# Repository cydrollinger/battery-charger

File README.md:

<a href="https://elec-real.com/case-studies/battery-charger/"></img></a>

>Electronic Realization L.L.C.								   
>Design: Battery charger 4 Li cells		   
>Engineer: Cy Drollinger								   
>Date: 5/18												           
>Email: cy@elec-real.com	
>Website: https://elec-real.com							   
>Address: 2023 Stadium Dr Suite 2B #210 Bozeman, MT 59715				   
>Phone: 406-539-8117	

**NOTE:**
 This design has been tested and functions as specified. The design is provided gratis, so, please 
 think critically while utilizing and or redesigning. Open electronic circuitry can be dangerous due 
 to easily shorting circuits which can generate immediate and intense heat resulting in fire. Conversation is
 welcome to improve this design and repository, but, be advised ER is a professional design house and
 monetary compensation is required for additional work toward this design enabling your success.			   

**PURPOSE:**
This is a hardware design that is capable of charging 4 Li ion cells. The design employs four different circuits
and charge currents: 100mA, 200mA, 400mA, and 800mA. The design files were created with Eagle Cadsoft v7.7 as a 
two layer board. Free Eagle version would be capable of viewing, and editing these files for redesign. 

>**File Arcitecture with a terse description**

* FOLDERS:
	* docs		: datasheets charging IC and battery holder
	* hardware	: eagle cadsoft(v7.7) hardware design files 	
		* eagleup		: 3D files 
		* library		: eagle part files 
		* manufacturing	: files required to produce the design
			* bom	: files created to order the parts
					* batteryCharger.txt	: 
					* batteryv1.1.csv	: digikey order
					* hundredUnits.txt	
			* gerber	: files generated to manufacture the board
			* <a href="https://oshpark.com/shared_projects/4os8OxLZ"></img></a>
	* readme.md	: this file

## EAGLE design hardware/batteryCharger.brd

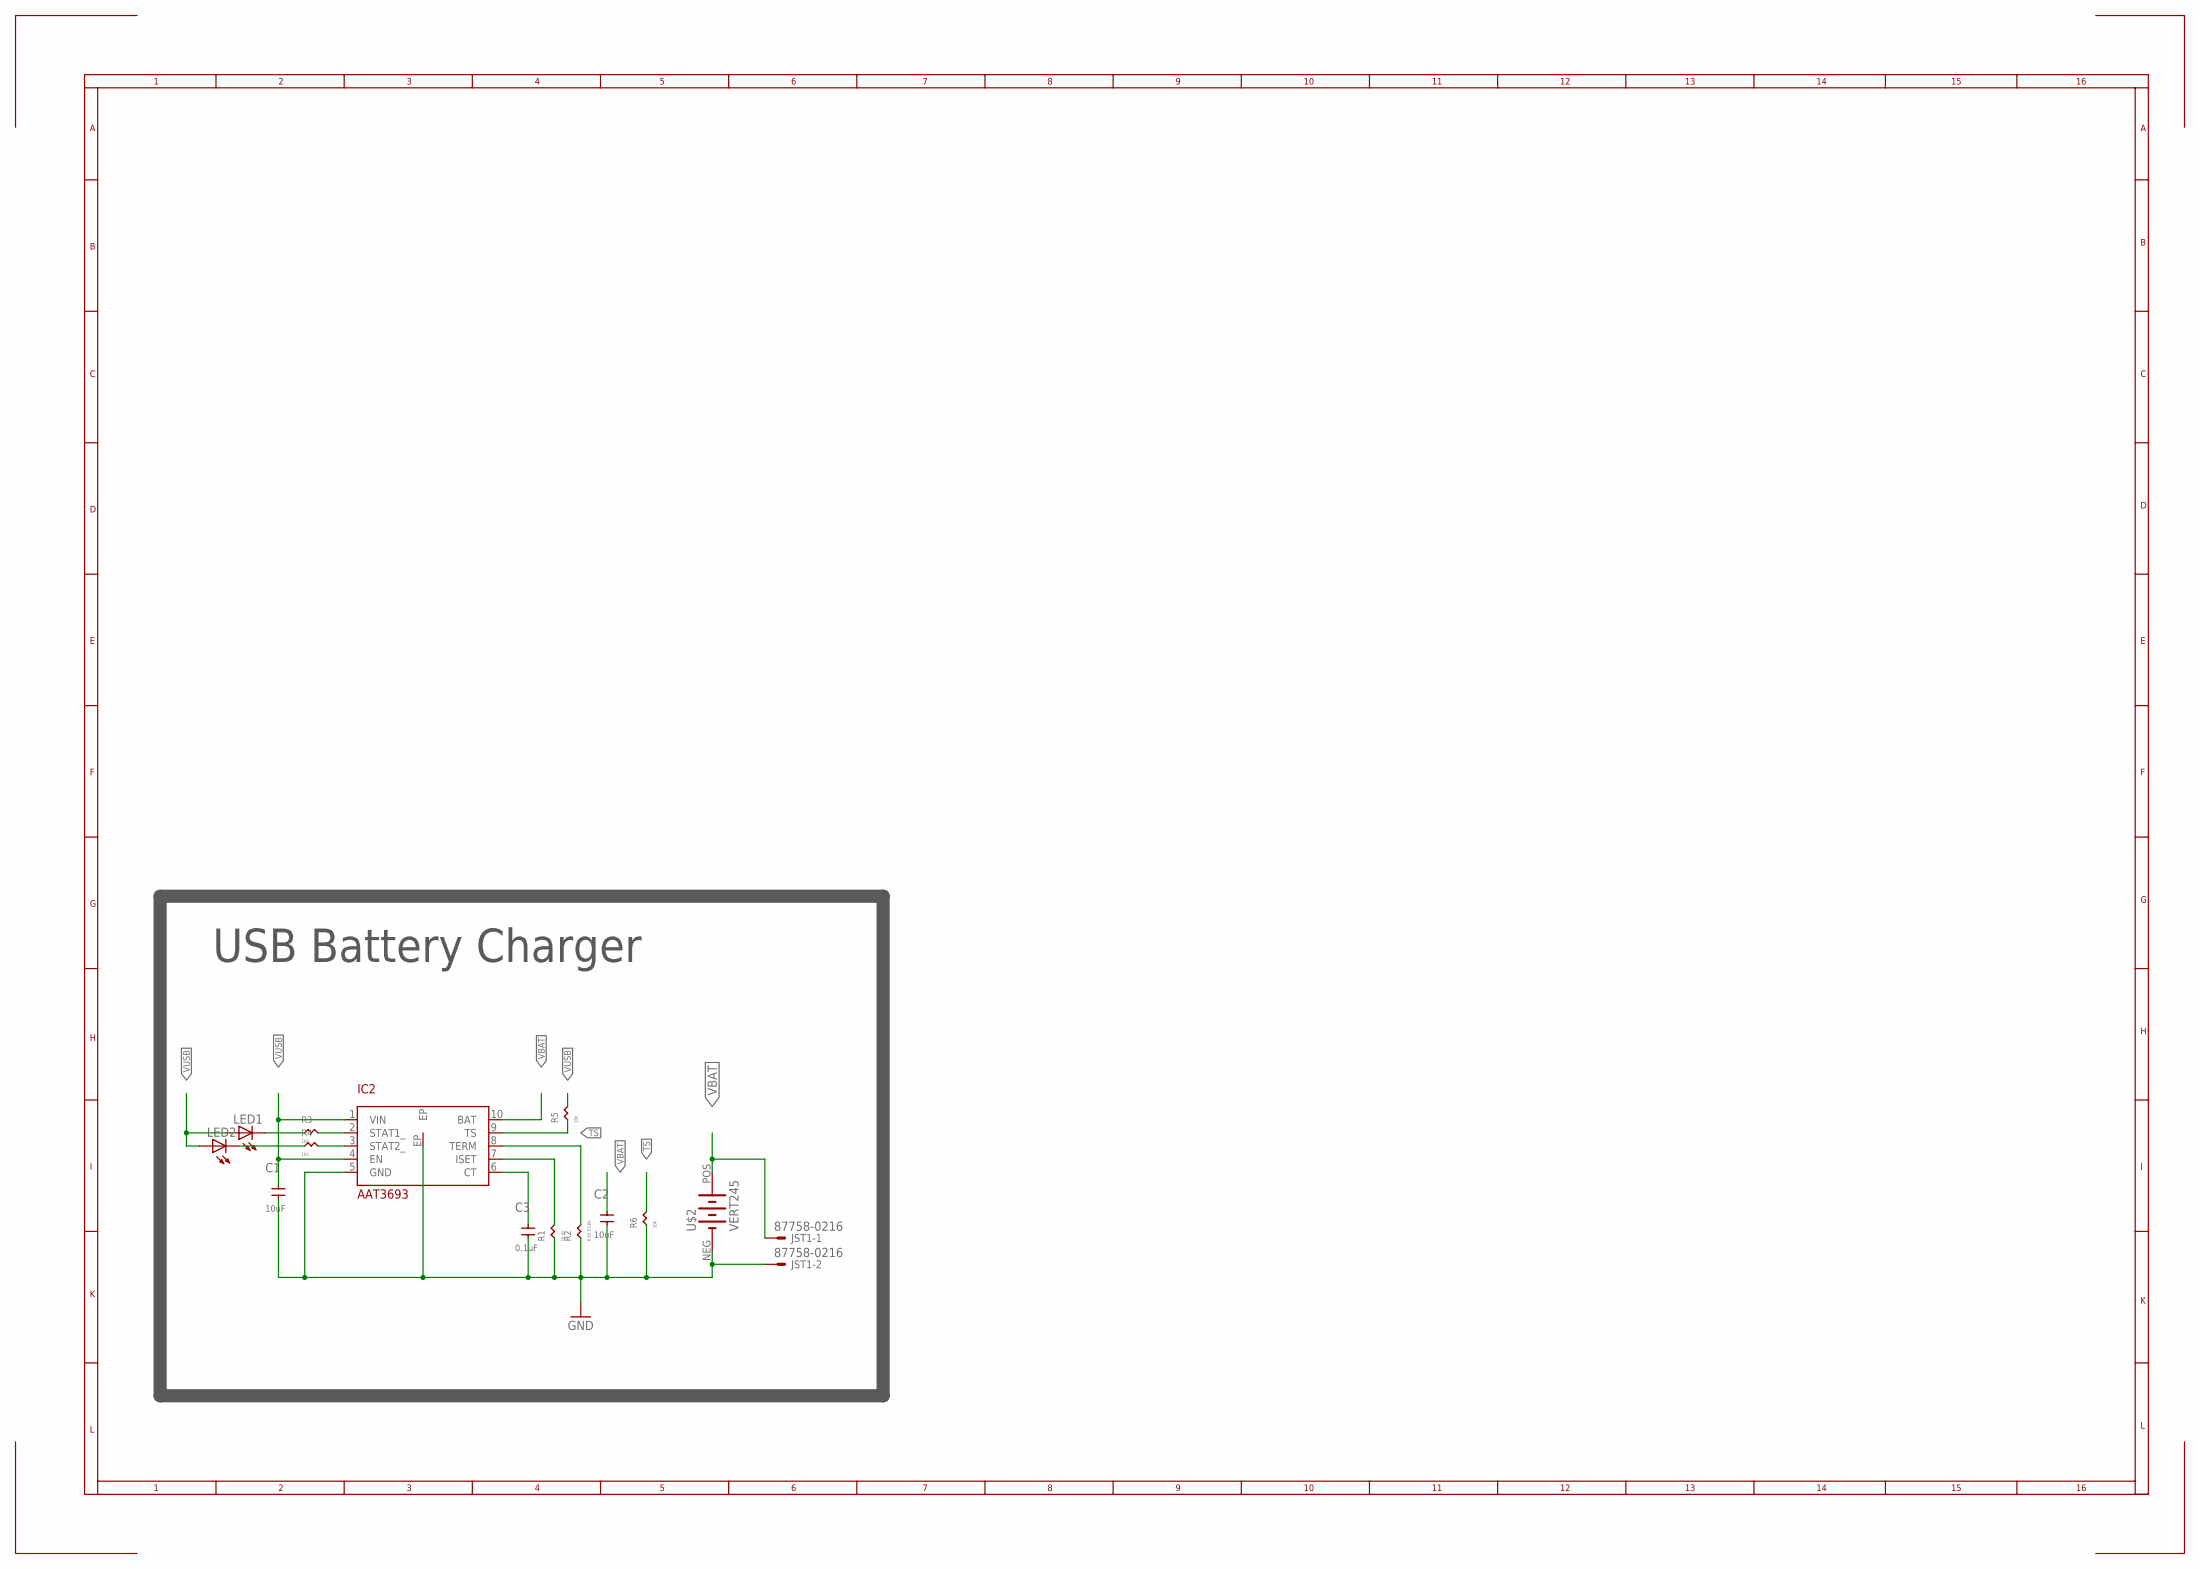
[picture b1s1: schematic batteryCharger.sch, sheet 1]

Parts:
C1, C2: 10uF; C0805
C3: 0.1uF; C0402
IC2: AAT3693
JST1: 87758-0216
LED1, LED2: LEDCHIP-LED0603; CHIP-LED0603
R1: 16.5k; R0402
R2: 6.65-53.6k; R0402
R3, R4: 1k5; R0402
R5, R6: 10k; R0402
U$2: VERT245

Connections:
GND: C1.1, C2.1, C3.1, IC2.5 (GND), IC2.EP, JST1.2, R1.1, R2.1, R6.1, U$2.NEG (-); also elsewhere on the board
unnamed: C3.2, IC2.6 (CT)
unnamed: IC2.7 (ISET), R1.2
unnamed: IC2.8 (TERM), R2.2
unnamed: IC2.3 (STAT2_), R4.2
unnamed: IC2.2 (STAT1_), R3.2
unnamed: LED1.C, R3.1
unnamed: LED2.C, R4.1
TS: IC2.9 (TS), R5.1, R6.2
VBAT: C2.2, IC2.10 (BAT), JST1.1, U$2.POS (+)
VUSB: C1.2, IC2.1 (VIN), IC2.4 (EN), LED1.A, LED2.A, R5.2; also elsewhere on the board

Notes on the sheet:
USB Battery Charger

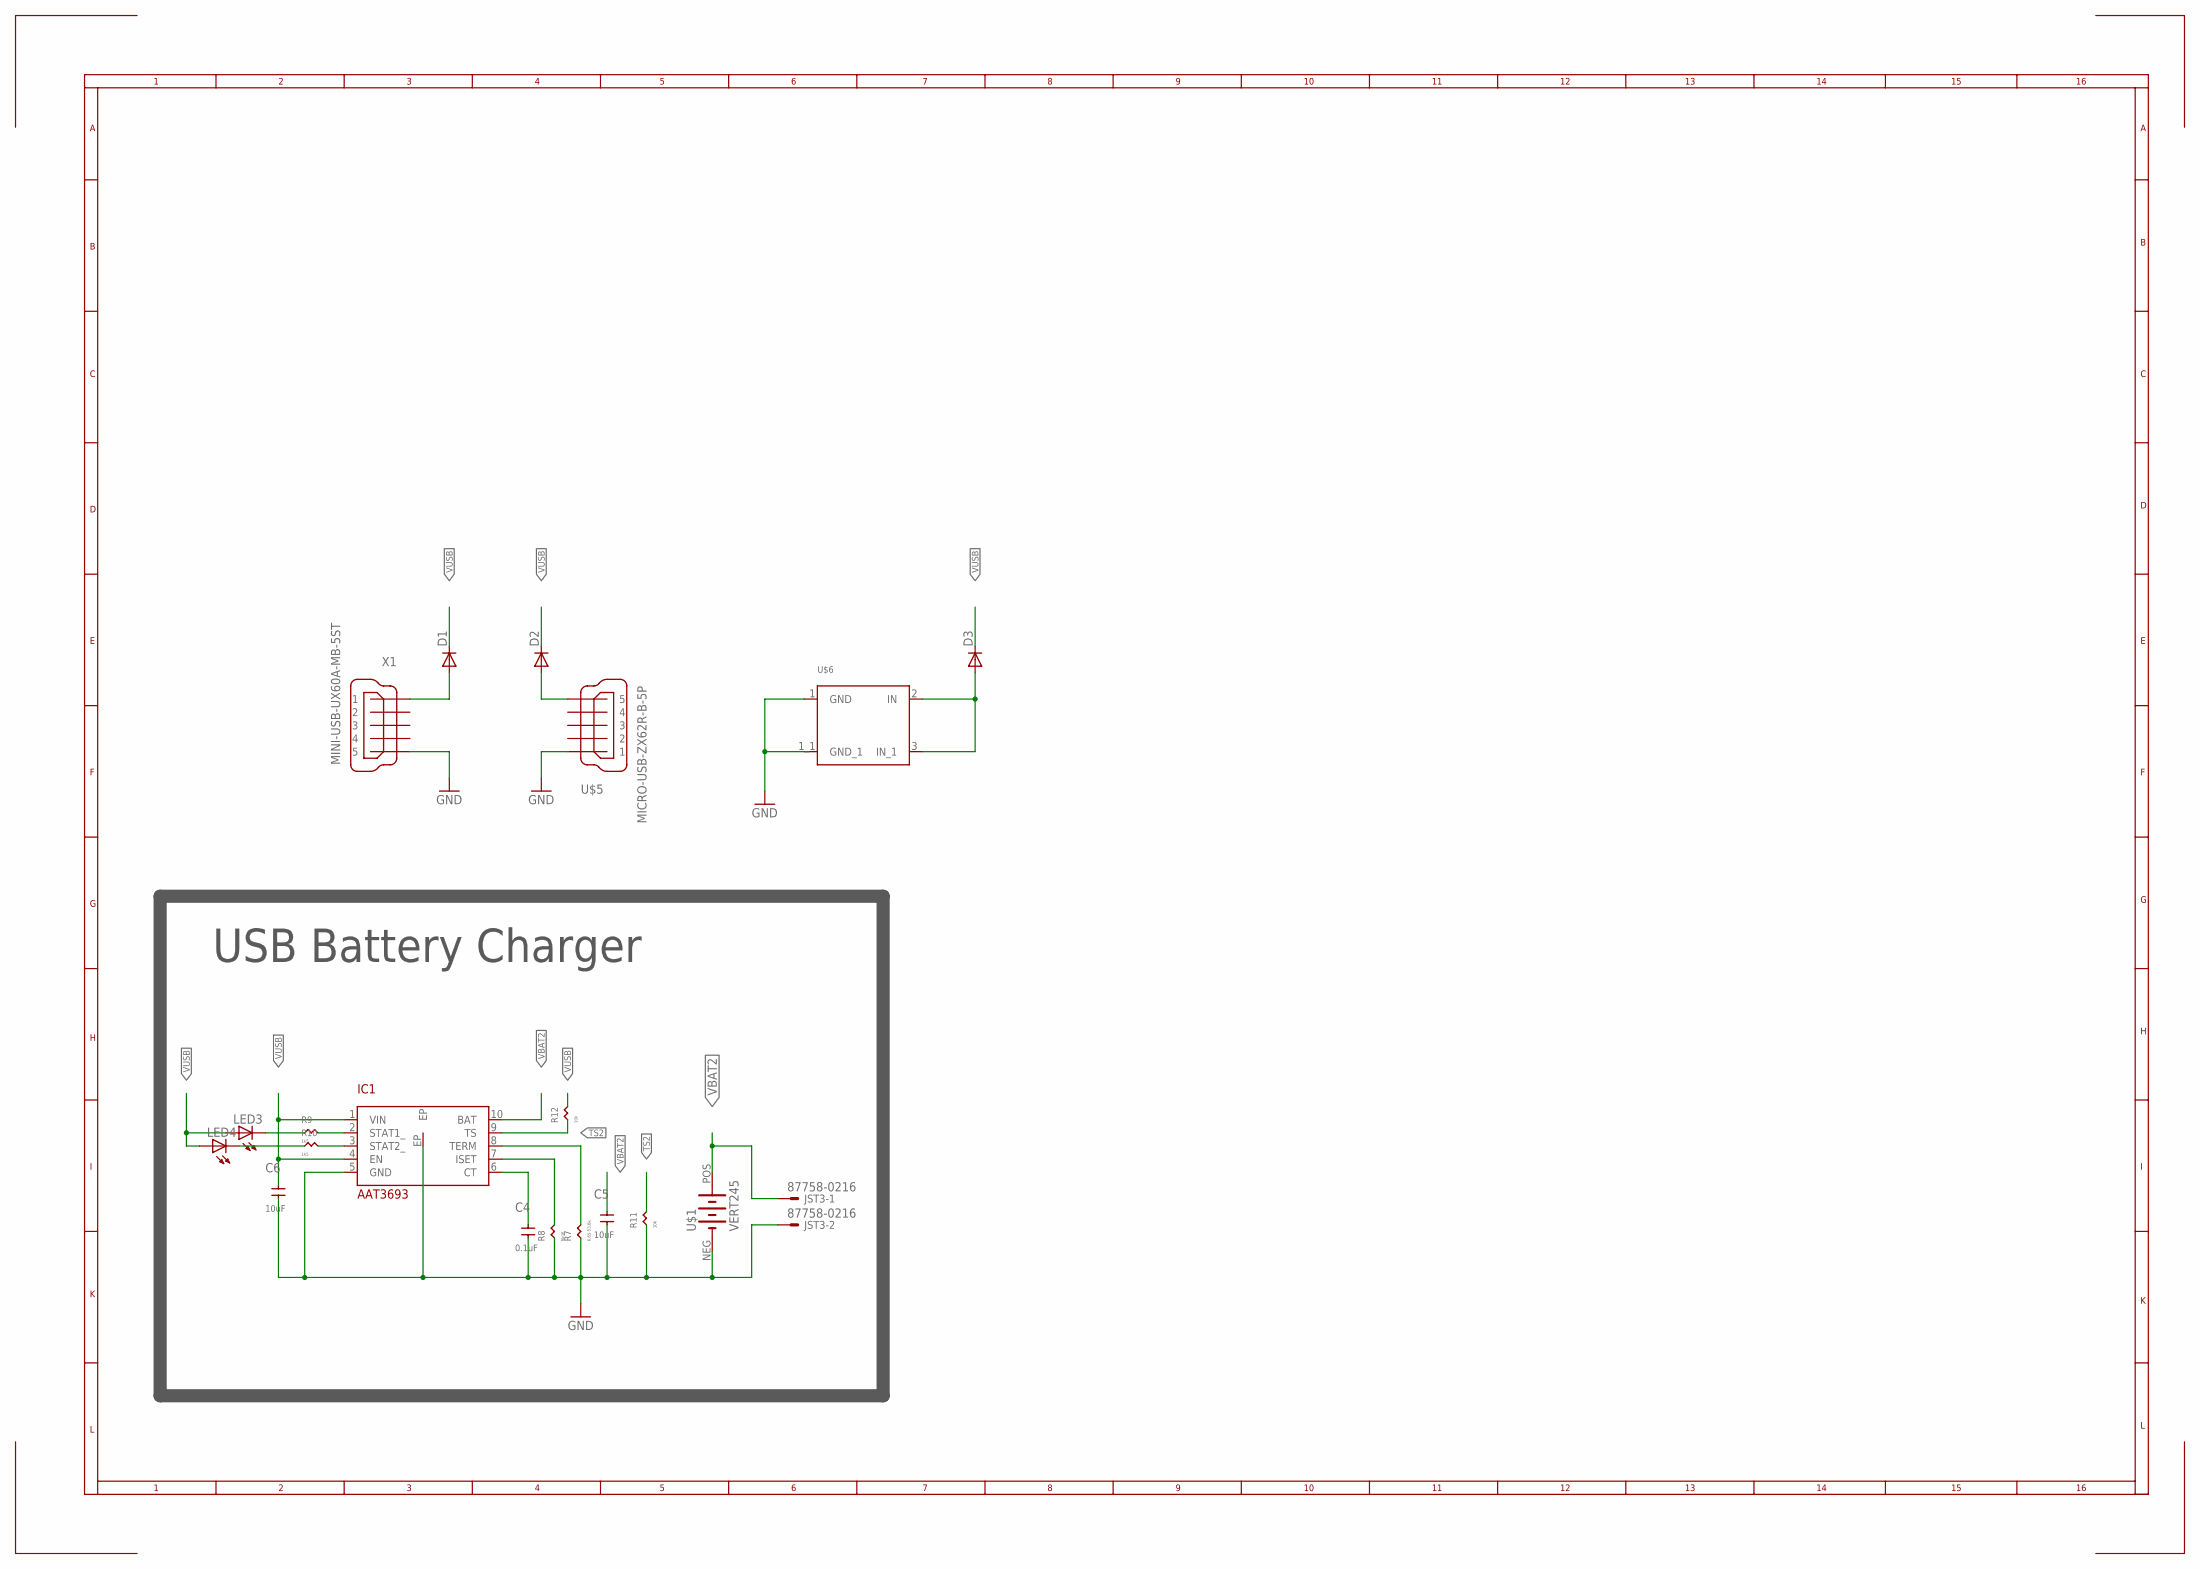
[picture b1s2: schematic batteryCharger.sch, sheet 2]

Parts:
C4: 0.1uF; C0402
C5, C6: 10uF; C0805
D1, D2, D3: DIODE-SOD323-R; SOD323-R; DIGIKEY BAT60AE6327HTSA1CT-ND
IC1: AAT3693
JST3: 87758-0216
LED3, LED4: LEDCHIP-LED0603; CHIP-LED0603
R7: 6.65-53.6k; R0402
R8: 8k06; R0402
R9, R10: 1k5; R0402
R11, R12: 10k; R0402
U$1: VERT245
U$5: MICRO-USB-ZX62R-B-5P; ZX62R-B-5P
U$6: PJ-002A_SMT
X1: MINI-USB-UX60A-MB-5ST; UX60A-MB-5ST

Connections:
GND: C4.1, C5.1, C6.1, IC1.5 (GND), IC1.EP, JST3.2, R7.1, R8.1, R11.1, U$1.NEG (-), U$5.1, U$6.1 (GND), U$6.1_1 (GND_1), X1.5; also elsewhere on the board
unnamed: C4.2, IC1.6 (CT)
unnamed: IC1.7 (ISET), R8.2
unnamed: IC1.8 (TERM), R7.2
unnamed: IC1.3 (STAT2_), R10.2
unnamed: IC1.2 (STAT1_), R9.2
unnamed: LED3.C, R9.1
unnamed: LED4.C, R10.1
unnamed: D1.A, X1.1
unnamed: D2.A, U$5.5
unnamed: D3.A, U$6.2 (IN), U$6.3 (IN_1)
TS2: IC1.9 (TS), R11.2, R12.1
VBAT2: C5.2, IC1.10 (BAT), JST3.1, U$1.POS (+)
VUSB: C6.2, D1.C, D2.C, D3.C, IC1.1 (VIN), IC1.4 (EN), LED3.A, LED4.A, R12.2; also elsewhere on the board

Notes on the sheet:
USB Battery Charger

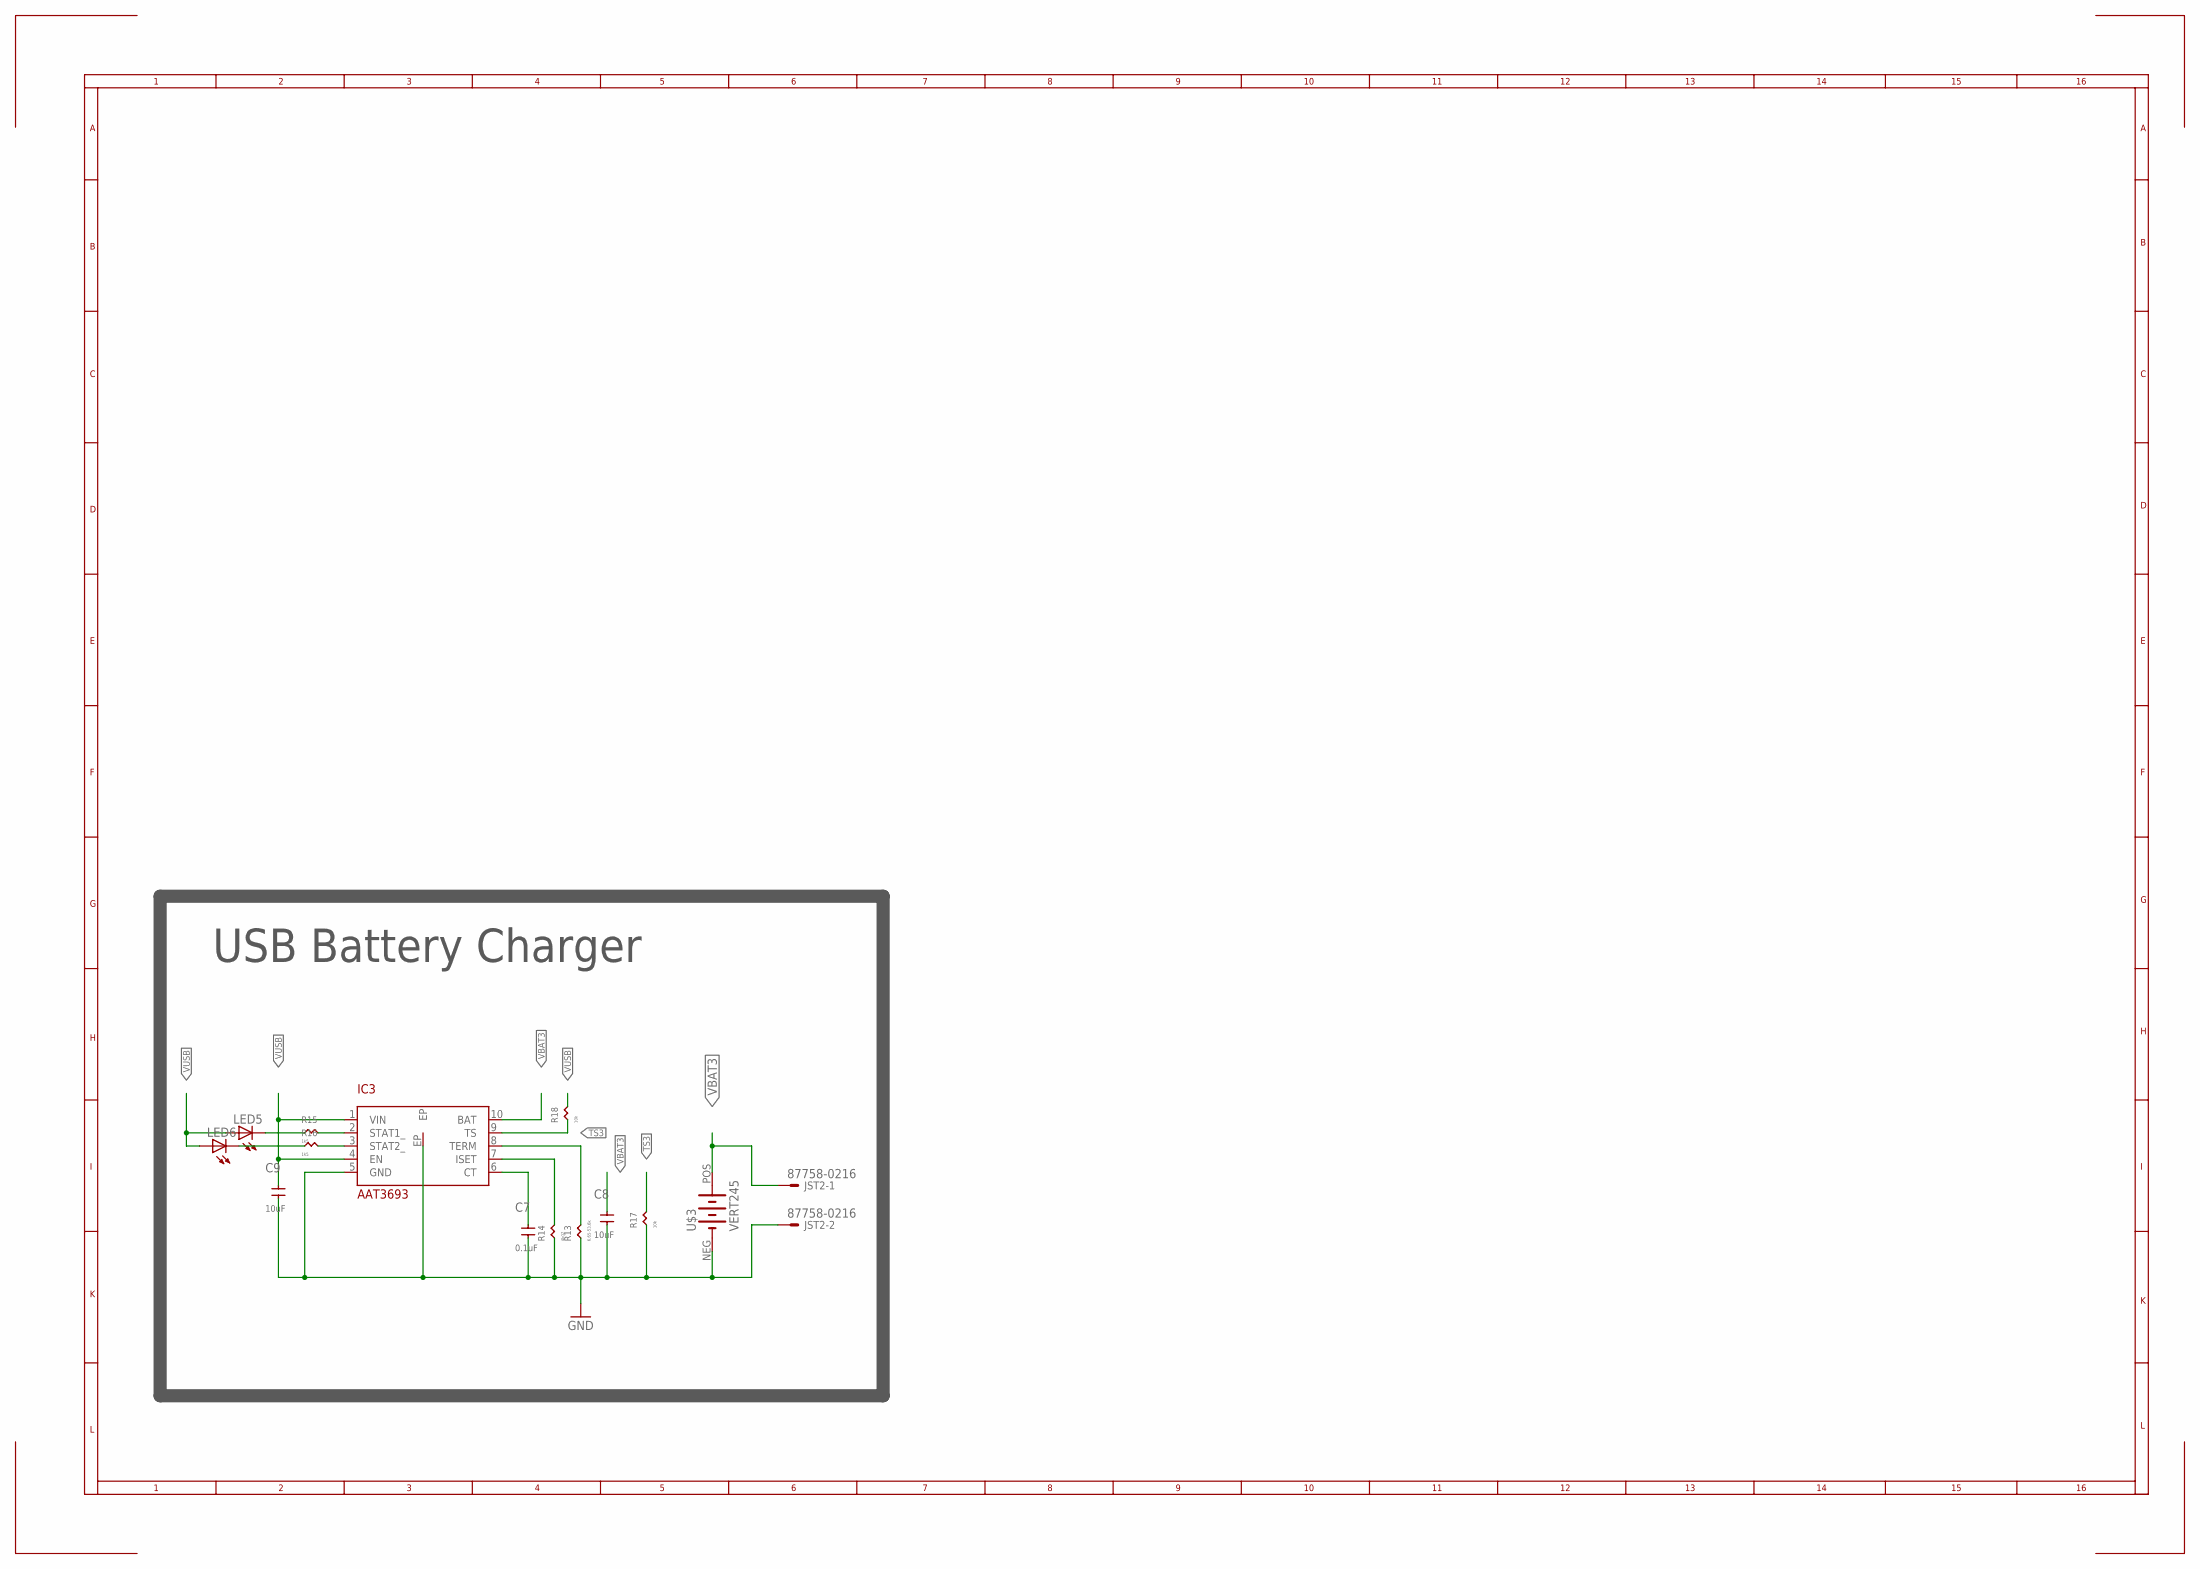
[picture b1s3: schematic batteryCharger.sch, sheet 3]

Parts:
C7: 0.1uF; C0402
C8, C9: 10uF; C0805
IC3: AAT3693
JST2: 87758-0216
LED5, LED6: LEDCHIP-LED0603; CHIP-LED0603
R13: 6.65-53.6k; R0402
R14: 4k02; R0402
R15, R16: 1k5; R0402
R17, R18: 10k; R0402
U$3: VERT245

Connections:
GND: C7.1, C8.1, C9.1, IC3.5 (GND), IC3.EP, JST2.2, R13.1, R14.1, R17.1, U$3.NEG (-); also elsewhere on the board
unnamed: C7.2, IC3.6 (CT)
unnamed: IC3.7 (ISET), R14.2
unnamed: IC3.8 (TERM), R13.2
unnamed: IC3.3 (STAT2_), R16.2
unnamed: IC3.2 (STAT1_), R15.2
unnamed: LED5.C, R15.1
unnamed: LED6.C, R16.1
TS3: IC3.9 (TS), R17.2, R18.1
VBAT3: C8.2, IC3.10 (BAT), JST2.1, U$3.POS (+)
VUSB: C9.2, IC3.1 (VIN), IC3.4 (EN), LED5.A, LED6.A, R18.2; also elsewhere on the board

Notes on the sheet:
USB Battery Charger

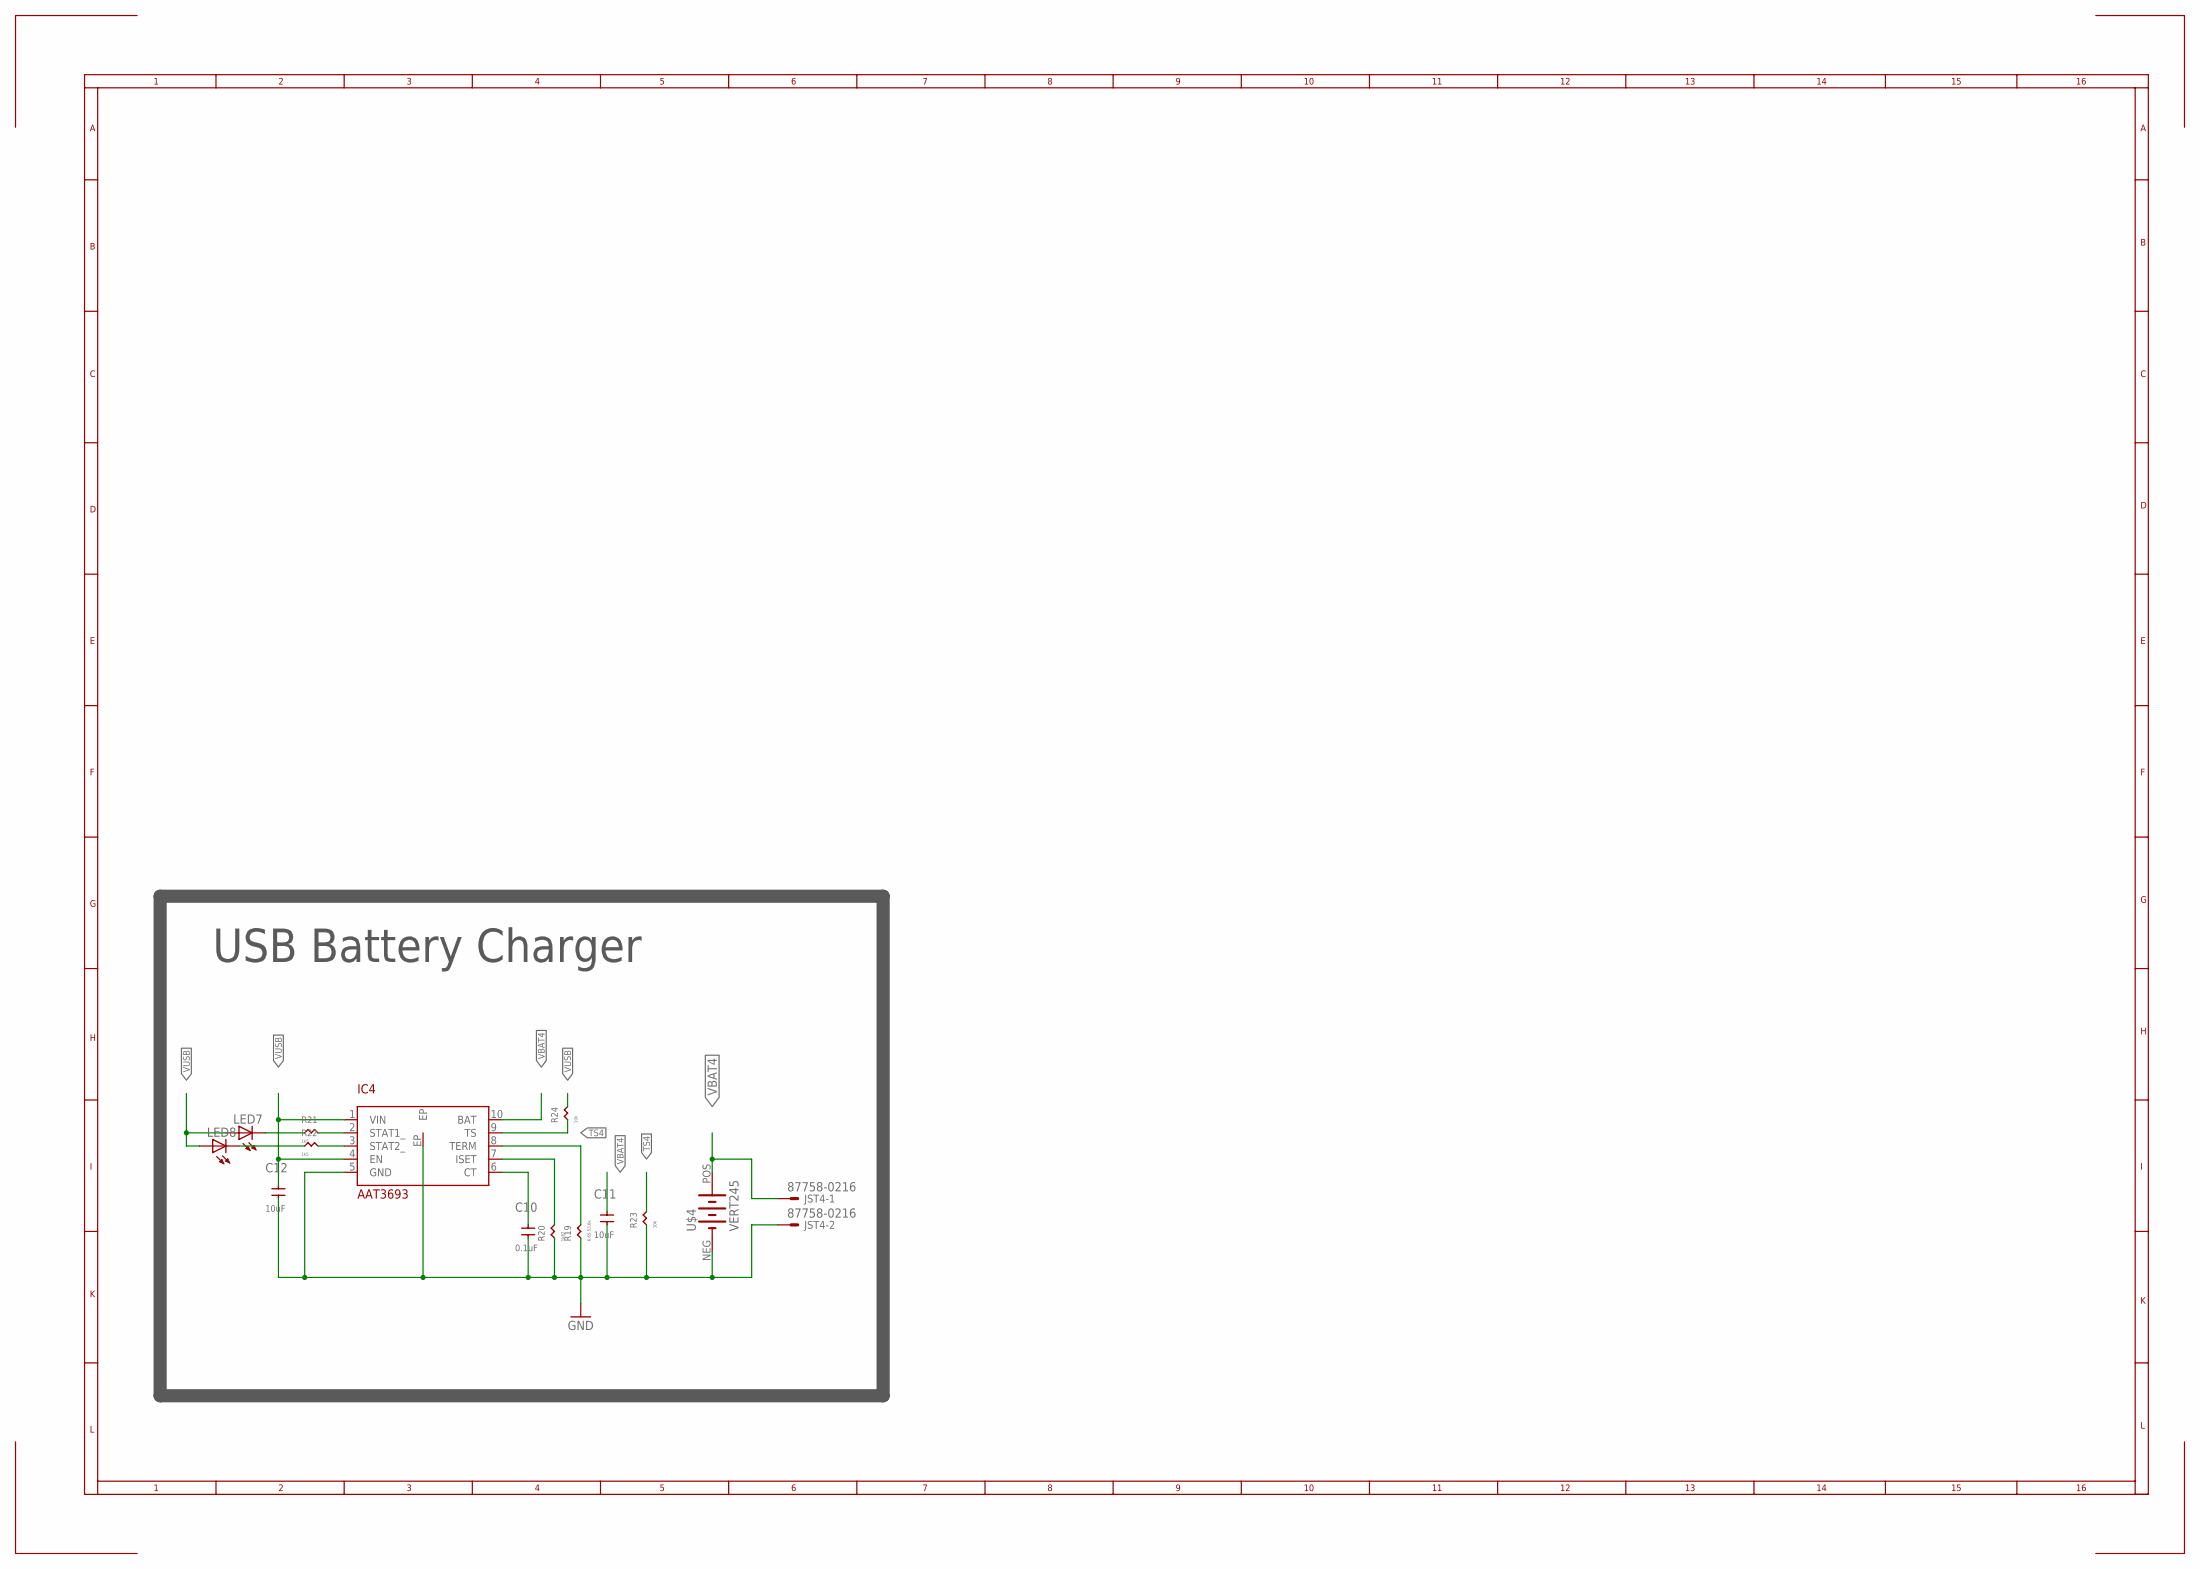
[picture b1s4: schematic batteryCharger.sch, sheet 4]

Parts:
C10: 0.1uF; C0402
C11, C12: 10uF; C0805
IC4: AAT3693
JST4: 87758-0216
LED7, LED8: LEDCHIP-LED0603; CHIP-LED0603
R19: 6.65-53.6k; R0402
R20: 1k87; R0402
R21, R22: 1k5; R0402
R23, R24: 10k; R0402
U$4: VERT245

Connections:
GND: C10.1, C11.1, C12.1, IC4.5 (GND), IC4.EP, JST4.2, R19.1, R20.1, R23.1, U$4.NEG (-); also elsewhere on the board
unnamed: C10.2, IC4.6 (CT)
unnamed: IC4.7 (ISET), R20.2
unnamed: IC4.8 (TERM), R19.2
unnamed: IC4.3 (STAT2_), R22.2
unnamed: IC4.2 (STAT1_), R21.2
unnamed: LED7.C, R21.1
unnamed: LED8.C, R22.1
TS4: IC4.9 (TS), R23.2, R24.1
VBAT4: C11.2, IC4.10 (BAT), JST4.1, U$4.POS (+)
VUSB: C12.2, IC4.1 (VIN), IC4.4 (EN), LED7.A, LED8.A, R24.2; also elsewhere on the board

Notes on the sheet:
USB Battery Charger

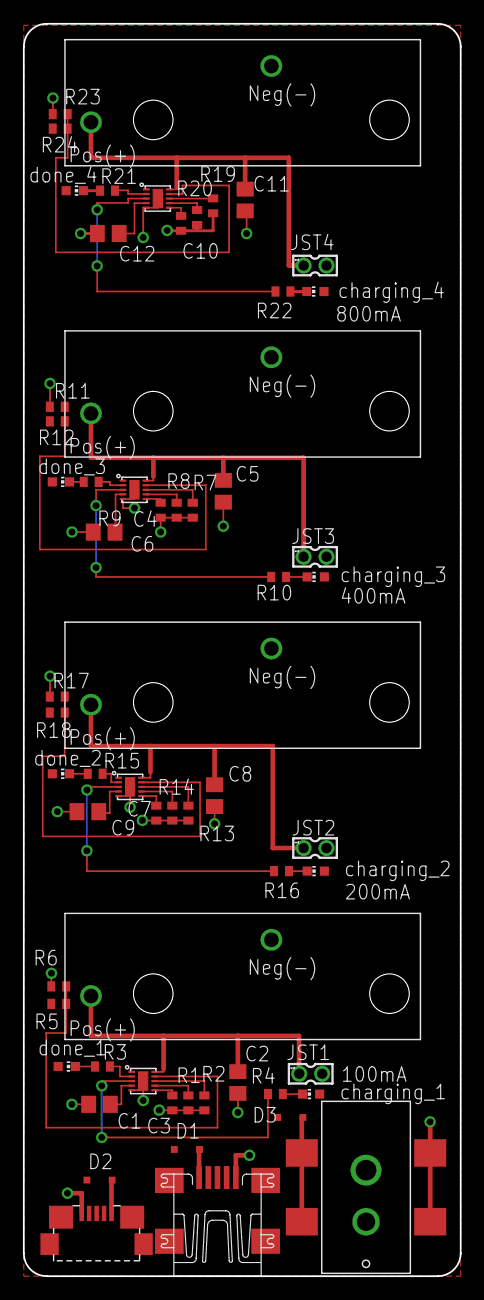
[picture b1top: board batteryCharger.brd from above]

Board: 2 copper layers, 38.1 x 109.2 mm, 62 parts (0 on the bottom side), 41 nets.

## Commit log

2019-04-16 First commit for elec-real.com 4/19
2019-04-17 First commit for elec-real.com 4/20
2019-04-18 first commit of files 4/18/19
2019-04-26 first commit 4/26/19
2019-04-27 first commit 4/27/19
2019-04-30 first commit 4/30/19
